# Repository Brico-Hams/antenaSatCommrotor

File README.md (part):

# PortableSatStation - estacion portable 145/435 MHz

**BricoHams · documentacion de ingenieria y montaje**

Accesos: [catalogo visual de todos los componentes inventariados](docs/assembly/components/README.md),
[instalacion visual y configuracion](docs/assembly/06-instalacion.md),
[montaje por modulos y conjunto](docs/assembly/README.md) y
[revision del proyecto y limites de verificacion](docs/PROJECT-REVIEW.md).

Laboratorio: [bancos y procedimientos reales](docs/testing/09-laboratorio.md),
[101 hojas de ensayo imprimibles](docs/testing/laboratorio/cuaderno.html) y
[registros CSV rellenables por ensayo/componente](docs/testing/laboratorio/README.md).
Incluye [NanoVNA](docs/testing/10-nanovna.md) y calibraciones; sin resultados
fisicos precargados ni autorizacion TX implicita.

## Nueva antena portable PF-01

El [rediseno PF-01](docs/ANTENNA-PORTABLE.md) toma como referencia visual
el cuerpo axial y los elementos radiales del video facilitado, sin copiar
medidas ni suponer compatibilidad RF. Propone boom dielectrico seccionado,
cuatro cassettes plegables y ocho puntas VHF desmontables. Objetivo de
paquete mecanico: **170 x 140 x 300 mm**, con verificacion geometrica
nominal, no ensayo de una antena fabricada.

Incluye [vista recogida](docs/assembly/portable/PF-folded.svg),
[BOM propia](bom/antenna-portable.csv), CAD, mallas candidatas y pruebas.
Es la nueva candidata de portabilidad; el rotor y los ejemplos anteriores
mantienen la antena historica hasta cualificar RF, masa, CG y montaje PF-01.

## Tres opciones TX/RX con previo de recepcion

La [comparativa de antenas](docs/ANTENNA-OPTIONS.md) permite escoger PF-01,
[Eggbeater](docs/ANTENNA-EGGBEATER.md) o [QFH](docs/ANTENNA-QFH.md).
Se incluyen modelos separados 145/435 MHz, vistas, BOM y montaje.
[Comunicaciones contrastadas con AMSAT](docs/SATELLITE-COMMS.md) y
[previo con bypass TX](docs/ANTENNA-PREAMPS.md): **25 W como techo de
diseno**, una sola cadena TX; sin homologacion ni habilitacion del PA.
Las redes QRP anteriores no quedan aprobadas para esa potencia.

## Idiomas / Languages / Nyelvek

La documentacion se prepara en espanol, ingles y hungaro. Las ediciones
inglesa y hungara estan en traduccion/sincronizacion y no se consideran
completas hasta comprobar cobertura y correspondencia con la revision
tecnica vigente. El indice de idiomas se enlazara al finalizar esas pruebas.
Los textos originales de licencias de terceros se conservan sin alteracion.

## Costes y materiales de referencia

La ampliacion incorporara precios de referencia en EUR para componentes,
materiales de montaje y consumibles, con cantidad, modelo/revision, fecha,
fuentes, IVA y portes. El promedio se calculara solamente con cotizaciones
comparables; una sola observacion se identificara como tal. Componentes
todavia sin modelo aprobado tendran una provision orientativa claramente
separada o precio pendiente, nunca coste cero ni precio inventado.
Las herramientas reutilizables se presupuestaran aparte del coste de la
estacion. Los pasos ilustrados se relacionaran con los identificadores de
la BOM para distinguir piezas, cables, fijaciones y materiales externos.
Las observaciones y categorias pendientes se conservan en
[reference-prices.csv](bom/reference-prices.csv), con metodo y limites en
[REFERENCE-PRICES.md](docs/REFERENCE-PRICES.md). El subconjunto electronico
cotizado suma 1313.90 EUR sin IVA normalizado; no es el coste de la estacion
completa. La recopilacion sigue abierta y no constituye presupuesto cerrado.

Diseno original modular de una estacion de radioaficionado para satelites:
antena plegable de dos bandas, rotor AZ/EL de dos ejes, controlador ESP32
con AP web y seguimiento local, compartimento RF desmontable y soporte RT3S.

**Autores actuales:** Anatol EA5KAO, Diego EA5JEF y Pedro Roca Molina.
Referencia de divulgacion cientifica para ninos y adolescentes:
[Bricohams](https://bricohams.org).
Ver [autoria](AUTHORS.md), [agradecimientos](ACKNOWLEDGEMENTS.md) y
[aviso de responsabilidad](DISCLAIMER.md). Uso educativo siempre supervisado.

**Estado: prototipo de ingenieria, no equipo RF/mecanico certificado.**
Los resultados de compilacion, pruebas y exportacion se registran en
[VALIDATION.md](docs/VALIDATION.md). Una compilacion o un STL valido NO
demuestra ROE, ganancia, resistencia al viento ni seguridad de una
estructura montada. No fabricar en serie ni transmitir sin el protocolo
de puesta en servicio.

## Base acordada

| Aspecto | Decision |
| --- | --- |
| Bandas | 145 y 435 MHz; canales concretos segun satelite y normativa |
| Motores | Dos NEMA 14; corriente/par segun ficha del motor elegido |
| Reduccion | BASE: dos etapas de correa GT2 20:100, total 25:1; planetarios como LEGACY |
| Material | ASA para piezas mecanicas; conductores y ejes metalicos |
| Seguimiento | SGP4 en ESP32; el movil no es el motor orbital |
| Red | AP sin Internet; STA con Internet o importacion manual de TLE |
| Radio | RT3S/OpenGD77 independiente; sin CAT/PTT automatico supuesto |
| Montaje | Tripode fotografico, inserto metalico y adaptadores de boom |
| Modularidad | Antena, rotor, radio y diplexor se separan |
| Masa | <=5 kg para conjunto operativo incluido tripode, radio y cables; bateria externa excluida por eleccion posterior; objetivo <=3 kg historico |
| Carga inicial | Objetivo a ensayar: antena <=0,5 kg, CG <=30 mm del eje EL |

**Cambio de prioridad aprobado:** la variante planetaria resulto demasiado
pesada en el presupuesto preliminar (3,208-4,038 kg con alimentacion).
El usuario autoriza una transmision mas ligera para priorizar <=3 kg.
La variante BASE conserva 25:1 y 80000 microsteps/vuelta, coordinados con
firmware. La geometria de montaje aun requiere verificacion fisica;
el calculo planetario original permanece
como comparativa, no como prueba de la variante ligera.

## Ampliacion en desarrollo: radio integrada multimodo

Esta seccion recoge las peticiones posteriores a la entrega inicial.
**No son prestaciones ya verificadas del hardware anterior ni de la APK
publicada localmente.** La tabla distingue alcance solicitado y estado;
las cifras medidas se registran en [VALIDATION.md](docs/VALIDATION.md).

| Funcion | Descripcion tecnica y limites | Estado de la ampliacion |
| --- | --- | --- |
| Radio de satelites VHF/UHF | 145/435 MHz nominales, frecuencias concretas segun satelite y normativa; cadenas RX/TX independientes para full-duplex | Arquitectura RF en verificacion; dos modulos seleccionados |
| Modos analogicos | FM, AM y SSB banda lateral superior (USB); USB aqui significa modo de modulacion, no conector | Solicitados; no se anuncian posibles en un modulo exclusivamente FM |
| CAT y Doppler | Control de frecuencia RX/TX y modo desde la misma APK; correccion dependiente de velocidad radial y plan de frecuencias | Integracion nueva pendiente; RT3S conserva operacion independiente sin CAT supuesto |
| Ordenador integrado | Raspberry Pi Compute Module 5 (CM5), CM5IO oficial, alimentacion y refrigeracion, para SDR, audio, SGP4 y rotor sin ESP32 | Arquitectura elegida; rendimiento conjunto, potencia y termica pendientes |
| Portadora y PCBA | CM5IO oficial adquirida mas placa auxiliar original para movimiento/sensores/protecciones | Eleccion confirmada; Gerbers/BOM/CPL de la auxiliar en desarrollo. No se fabrica una portadora CM5 unica personalizada en esta revision |
| Modulos RF | Dos LimeSDR Mini reemplazables, uno por banda para recepcion VHF/UHF simultanea; ambos capaces de TX; SMA convencional 50 ohm | Eleccion vigente; un solo TX activo inicialmente. Salida nativa de baja potencia, no 5 W: PA lineales y filtros requieren cualificacion fisica |
| Movimiento bajo Linux | Generador de movimiento dedicado en drivers, limites NC, corte fisico de potencia y watchdog independiente | Drivers y placa nueva pendientes; no generar STEP con un bucle no determinista y declarar precision |
| GNSS/GPS | Receptor y antena para sitio, altitud y UTC de SGP4; interfaz UART y PPS solo con niveles/protocolo documentados y verificados | GNSS NMEA implementado en variante ESP32; receptor/interfaz SBC y antena por seleccionar; PPS opcional y no verificado; GNSS estacionario no da rumbo |
| Brujula | Magnetometro remoto, calibracion del conjunto instalado, declinacion por sitio/fecha y referencia de norte verdadero | Compass/magnetometro nuevo no implementado ni calibrado; sensor, montaje, interfaz y PCB pendientes; conectores opcionales previos no implican brujula funcional |
| Inclinacion/nivel | IMU mide inclinacion de la base para compensacion de inclinacion de brujula; no es elevacion de antena | IMU, montaje, interfaz y calibracion nuevos pendientes; cableado/pines TBD hasta congelar PCB |
| Posicion de ejes | Tres encoders de salida independientes AZ/EL/POL y seis finales NC independientes (dos por eje); homing y limites conservadores | Tres canales de feedback y seis entradas por disenar. Tres AS5600 comparten direccion I2C 0x36: buses separados o multiplexor concreto y verificado; no asumir bus comun |
| Audio Bluetooth | Bidireccional: recepcion a Android y envio de voz/AFSK hacia radio; transporte PCM transparente separado del BLE del rotor | Protocolo y caudal en desarrollo; no atribuir audio a las tramas de control actuales |
| Audio local | Altavoz pequeno y microfono integrados; accesorio externo tipo Baofeng/K1 con jacks separados de 3,5/2,5 mm | No son conectores SMA ni de alimentacion; pinout, bias, PTT y compatibilidad exacta pendientes; no cablear por apariencia |
| SSTV en Android | Recepcion y reconstruccion de imagenes ISS PD120/PD180 desde audio | Decodificador y vectores de prueba en desarrollo |
| Funciones tipo Look4Sat/Robot36 | Primera version acordada: catalogo/pases, mapa/radar, avisos, frecuencias/Doppler, tres ejes, SSTV ISS y mensajeria APRS | Matriz funcional y desarrollo por etapas; no se promete paridad completa ni todos los modos Robot36 |
| Digitales en Android | Bell202 AFSK1200, AX.25 con NRZI, bit stuffing y CRC; interpretacion APRS | Desarrollo y pruebas PCM pendientes; no incluye automaticamente otros protocolos digitales |
| Mensajes APRS | Recepcion, redaccion y envio entre indicativos, destinatario, ID y ACK/rej | Codificacion de audio y transporte RF se verifican por separado; un WAV no demuestra transmision ni entrega |
| SMS celular | No solicitado en la seleccion final: APRS entre indicativos no es SMS a un numero de telefono | Sin pasarela movil ni promesa de entrega |
| PCB/Gerbers actualizados | Nueva portadora de ordenador, motores, audio y protecciones, con modulos RF desmontables | Revision separada pendiente de componentes/pinouts; no usar la aprobacion ERC/DRC anterior |
| Ensamblaje JLCPCB | Paquete de Gerbers/taladros, BOM PCBA y CPL pick-and-place con referencias, coordenadas, cara y rotacion; listado separado de modulos/manual/DNP | Solicitado; pendiente de placa rutada, LCSC exactos y verificacion. No se ha enviado una orden |
| Caja y energia | Branding Bricohams, acceso a conectores, blindaje RF metalico, ventilacion, bateria y protecciones | Reabrir cotas, consumo, temperatura y masa tras seleccionar hardware |
| Autonomia | Objetivo 2 horas con dos receptores activos y transmision intermitente; incluir CM5, Bluetooth, sensores y tres ejes | Consumo, porcentaje TX, capacidad util y eficiencia pendientes de medida; no duracion garantizada |
| Tercer eje POL | Motor para giro axial limitado de la antena, posicion calibrada, limites fisicos y paso protegido de coaxiales | Diseno y recalculo de masa, cargas, transmision y tres canales de motor en desarrollo |
| Seleccion RHCP/LHCP | Conmutacion RF de alimentacion/fase en antena circular compatible, distinta del giro mecanico POL | Redes por banda y conmutacion con TX inhibido pendientes de diseno y medida |
| Conectores RF | SMA convencional de 50 ohm en antena, diplexor VHF/UHF, hibrido/puertos CP, LimeSDR/radio y bulkheads | Eleccion vigente para aligerar; no RP-SMA, BNC de base ni cadenas de adaptadores. Verificar pin/socket central y genero de acoplamiento en cada pieza; masa, soporte, alivio y par del fabricante TBD. BNC solo opcion heredada |
| USB-C | Preferencia para alimentacion y datos; conservar SMA RF, K1 audio y Bluetooth bidireccional | Verificar rol host/provisionamiento, velocidad, tension y negociacion/cable de potencia por puerto; no asumir un unico puerto para todo |
| Alimentacion Powerpole y fusibles | Powerpole rojo/negro en enlace bateria externa/estacion, fusible principal cerca del positivo de bateria y fusibles por rama CM5/motores/RF | Seleccionar contactos/cable/portafusibles DC y calibres segun carga, inrush y proteccion del conductor; BMS no sustituye fusibles |
| EMI de alimentacion | Evaluar choque de modo comun, filtro diferencial amortiguado y desacoplos por rama; separar retorno/potencia de motores, conversores y RF | Corriente/saturacion/DCR, estabilidad del convertidor, transitorios y ruido recibido requieren medidas; no aislamiento RF garantizado |
| Sistema operativo BricoHams | Derivado de Raspberry Pi OS oficial ARM64 para CM5, banner/branding originales, dependencias y servicios del proyecto, aprovisionamiento privado local | Receta/CI en desarrollo; no imagen arrancada o flasheada verificada. Arranque sin movimiento/PTT y puesta en servicio explicita |

Las referencias [(tr)uSDX](https://dl2man.de/) y
[uSDX SOTA](https://antrak.org.tr/blog/usdx-sota-modular-all-mode-sdr-hf-transceiver-for-qrp-operations/)
orientan modularidad, formato y control CAT, pero son equipos **HF**:
no se escalan a 145/435 MHz cambiando solamente el firmware.
El [ATU-100](https://github.com/Dfinitski/N7DDC-ATU-100-mini-and-extended-boards)
es un acoplador, no un transceptor, filtro de aislamiento o diplexor VHF/UHF.
No se copian sus disenos ni se sustituyen sus licencias por las del proyecto.

Para full-duplex se deben medir aislamiento, bloqueo y desensibilizacion
del receptor durante TX en ambas combinaciones VHF/UHF, ademas de ROE,
armónicos y temperatura. Ningun valor de potencia, sensibilidad, autonomia,
latencia o precision de esta ampliacion se considera garantizado.
PTT debe quedar desactivado en arranque, fallo, perdida de enlace o expiracion
del permiso; transmision requiere autorizacion y puesta en servicio fisica.
La compresion de voz y la supresion de ruido pueden impedir SSTV/AFSK;
una conexion Bluetooth correcta no prueba que el audio digital sea util.
Girar una antena circular alrededor de su eje no invierte RHCP/LHCP:
la seleccion de mano necesita una red RF adecuada y ensayos de relacion
axial, fase y aislamiento. El tercer motor no existia en el rotor AZ/EL
anterior; sus drivers, limites y presupuesto no cubren el nuevo eje.

La primera entrega ESP32, su firmware/WebFlash, la APK y Gerbers anteriores
siguen siendo la variante documentada de referencia, no una implementacion
de la radio nueva. ### Matriz de variantes y evidencia (AUD-06)

| Generacion | Contenido | Pruebas que le aplican | Estado |
| --- | --- | --- | --- |
| ESP32 + RT3S (primera entrega) | ESP32 SGP4, WebFlash, APK ESP32 | 29 pruebas JVM, Node, firmware | Referencia historica; NO es aceptacion de CM5 |
| Intermedia (1-2 SDR) | Etapas del ADR-024 a ADR-026 | Pruebas de contrato de la etapa | Superada |
| CM5 + 2 LimeSDR Mini + AZ/EL/POL | Auxiliar CM5 rutada, Android CM5 | 58 pruebas JVM, 377 comprobaciones de contrato, ERC/DRC 0/0 | Prototipo DIGITAL; NO FABRICAR, NO ENERGIZAR, NO HABILITAR PTT |

Digital, fabricable y seguro operacionalmente son hitos distintos. Resultados
heredados de una generacion no se presentan como aceptacion de otra.

Si se adopta Raspberry Pi, su instalacion/aprovisionamiento
sera distinto de WebFlash ESP32. Consulte las decisiones
[ADR-024 a ADR-026](docs/ARCHITECTURE.md) y la trazabilidad
[R25 a R33](docs/REQUIREMENTS.md).

### Ubicacion, orientacion y sensores

El GNSS quieto **no mide el rumbo de la estacion**: proporciona sitio/UTC;
un rumbo deducido del movimiento no sustituye al norte verdadero del rotor.
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
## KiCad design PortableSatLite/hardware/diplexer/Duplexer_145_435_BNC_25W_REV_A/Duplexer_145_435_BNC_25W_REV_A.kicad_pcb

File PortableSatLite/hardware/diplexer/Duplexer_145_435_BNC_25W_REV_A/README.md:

DUPLEXER 145 / 435 MHz — BNC — 25 W TARGET — REV A

Architecture
  J1 ANT -> 5th-order Chebyshev LPF -> J2 VHF
  J1 ANT -> 5th-order Chebyshev HPF -> J3 UHF

Filter values are based on the published KI0AG 2m/70cm micro-duplexer:
  LPF: 68 nH, 18 pF, 100 nH, 18 pF, 68 nH
  HPF: 4.7 pF, 16 nH, 3.1 pF, 16 nH, 4.7 pF

Target bands:
  VHF: 144–146 MHz, nominal 145 MHz
  UHF: 430–440 MHz, nominal 435 MHz
  System impedance: 50 ohm
  Power target: 25 W

25 W NOTE
The published KI0AG board was described as a 10 W design. This REV A adapts the
component technology and mechanical construction for a 25 W target, but it is
NOT a laboratory-validated 25 W rating. Verify with a 50-ohm dummy load and VNA.
Start at low power and increase progressively. Check insertion loss, return loss,
and inter-port isolation before connecting radios.

BNC
J1-J3 are specified as TE Connectivity 5415025-1, 50 ohm, 4 GHz, right-angle,
panel-mount, through-hole BNC. The manufacturer explicitly says to use its product
drawing for design activity. The custom footprint in this project is a working
prototype footprint; VERIFY the exact hole pattern against the manufacturer's
drawing before ordering PCBs.

PCB
  80 x 60 mm
  2-layer FR-4, 1.6 mm
  2 oz copper recommended
  Full B.Cu ground plane
  F.Cu ground guard + stitching vias
  Metal enclosure strongly recommended

Tuning
  Measure all 3 ports with a VNA at low power.
  Tune air-core inductors and, if needed, replace C4 by 3.0/3.3 pF or add a tiny
  parallel C0G tuning pad. Do not apply 25 W until the RF response is verified.

Files
  *.kicad_pcb : PCB
  *.kicad_sch : KiCad 8 schematic project record (textual engineering schematic)
  *.sch       : legacy KiCad schematic with actual component symbols; open and
                save in KiCad to convert to a native .kicad_sch.
  fabrication/ : Gerber and Excellon files

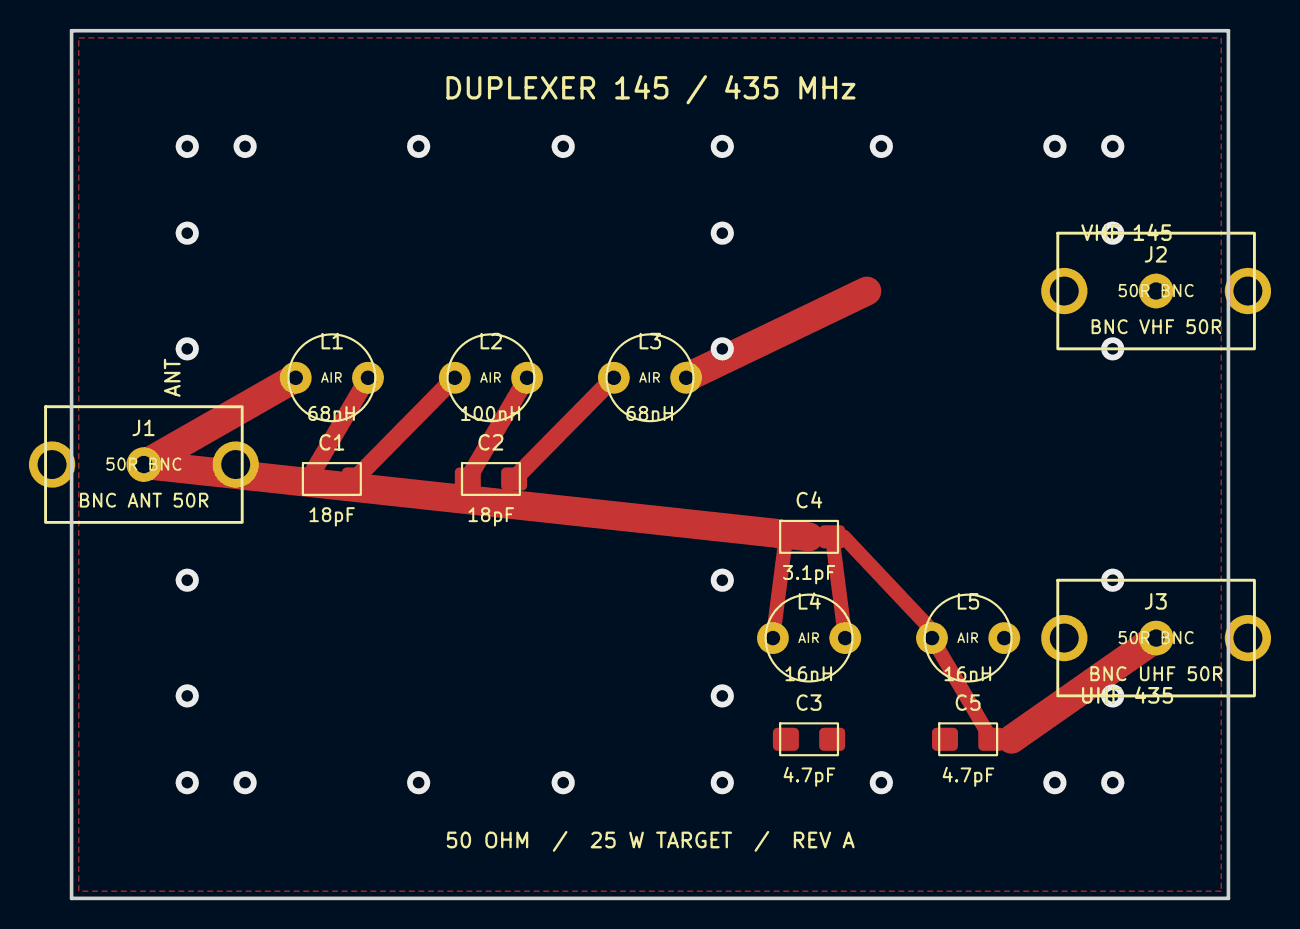
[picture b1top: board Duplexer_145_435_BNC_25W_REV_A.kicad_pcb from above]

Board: 2 copper layers, 80.0 x 60.0 mm, 13 parts (0 on the bottom side), 8 nets.

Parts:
C1: 18pF; C1
C2: 18pF; C2
C3: 4.7pF; C3
C4: 3.1pF; C4
C5: 4.7pF; C5
J1: BNC ANT 50R; J1
J2: BNC VHF 50R; J2
J3: BNC UHF 50R; J3
L1: 68nH; L1
L2: 100nH; L2
L3: 68nH; L3
L4: 16nH; L4
L5: 16nH; L5

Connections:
ANT: C3.1, J1.1, L1.1
GND: C1.2, C2.2, J1.2, J1.3, J2.2, J2.3, J3.2, J3.3, L4.2, L5.2
HP1: C3.2, C4.1, L4.1
HP2: C4.2, C5.1, L5.1
LP1: C1.1, L1.2, L2.1
LP2: C2.1, L2.2, L3.1
UHF: C5.2, J3.1
VHF: J2.1, L3.2

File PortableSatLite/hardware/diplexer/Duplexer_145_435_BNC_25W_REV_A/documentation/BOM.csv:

Ref,Value,Footprint/part,Qty,Notes
J1,BNC ANT,TE Connectivity 5415025-1,1,"50 ohm, panel mount, right angle, THT"
J2,BNC VHF,TE Connectivity 5415025-1,1,"50 ohm, panel mount, right angle, THT"
J3,BNC UHF,TE Connectivity 5415025-1,1,"50 ohm, panel mount, right angle, THT"
L1,68 nH,AIR-COIL-4MM,1,"~5 turns, 0.8-1.0 mm Cu, tune on VNA"
C1,18 pF,C0G-HV-1206,1,"1 kV preferred, C0G/NP0"
L2,100 nH,AIR-COIL-4MM,1,"~6 turns, 0.8-1.0 mm Cu, tune on VNA"
C2,18 pF,C0G-HV-1206,1,"1 kV preferred, C0G/NP0"
L3,68 nH,AIR-COIL-4MM,1,"~5 turns, 0.8-1.0 mm Cu, tune on VNA"
C3,4.7 pF,C0G-HV-1206,1,"1 kV preferred, C0G/NP0"
L4,16 nH,AIR-COIL-4MM,1,"~2.5 turns, 0.8-1.0 mm Cu, tune on VNA"
C4,3.1 pF,C0G-HV-1206,1,1 kV preferred; 3.0 pF + parasitic is acceptable
L5,16 nH,AIR-COIL-4MM,1,"~2.5 turns, 0.8-1.0 mm Cu, tune on VNA"
C5,4.7 pF,C0G-HV-1206,1,1 kV preferred
PCB,80 x 60 mm,"2-layer FR-4, 1.6 mm, 2 oz Cu",1,ENIG preferred; metal enclosure recommended
J1-J3,BNC 50 ohm,TE Connectivity 5415025-1,3,Verify mechanical drawing before fabrication

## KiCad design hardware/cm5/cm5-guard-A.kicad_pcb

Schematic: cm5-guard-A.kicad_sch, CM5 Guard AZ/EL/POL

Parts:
C1, C2, C10, C11: 1u; C_0603_1608Metric; MPN GRM188R71C105KA12D
C3, C4, C5, C6, C7, C8, C9, C12, C13, C14, C15, C17, C18, C19, C20, C21, C22, C23, C24, C25: 100n; C_0603_1608Metric; MPN GRM188R71C104KA01D
C16: 100n; C_0603_1608Metric; MPN GRM188R71C104KA01D; not fitted
C80: 47u 50V candidate; CP_Radial_D6.3mm_P2.50mm; MPN EEU-FR1H470; not fitted
D1: BZT52C12 12V; D_SOD-123; MPN BZT52C12-7-F; not fitted
D2: SMBJ18A candidate; D_SMB; MPN SMBJ18A; not fitted
F1: MAIN INSERT TBD - EMPTY; FuseHolder_Blade_ATO_Littelfuse_FLR_178.6165; MPN 178.6165.0001; not fitted
F2, F3, F4, F5, F6: BRANCH INSERT TBD - EMPTY; FuseHolder_Blade_ATO_Littelfuse_FLR_178.6165; MPN 178.6165.0001; not fitted
J1: CM5IO GPIO VIO=3V3 ONLY; IDC-Header_2x20_P2.54mm_Vertical; MPN 3020-40-0300-00
J2: ISOLATED 5V external PSU; PinHeader_1x02_P2.54mm_Vertical; not fitted
J3: AZ AS5600 0x36; JST_PH_B4B-PH-K_1x04_P2.00mm_Vertical; MPN B4B-PH-K-S(LF)(SN)
J4: EL AS5600 0x36; JST_PH_B4B-PH-K_1x04_P2.00mm_Vertical; MPN B4B-PH-K-S(LF)(SN)
J5: POL AS5600 0x36; JST_PH_B4B-PH-K_1x04_P2.00mm_Vertical; MPN B4B-PH-K-S(LF)(SN)
J6: LIS3MDL; JST_PH_B4B-PH-K_1x04_P2.00mm_Vertical; MPN B4B-PH-K-S(LF)(SN)
J7: LSM6DSOX; JST_PH_B4B-PH-K_1x04_P2.00mm_Vertical; MPN B4B-PH-K-S(LF)(SN)
J8: GNSS PID746 custom harness; PinHeader_1x05_P2.54mm_Vertical; MPN M20-9990545
J9: AZ_LIMIT_MIN_N NC contact; PinHeader_1x02_P2.54mm_Vertical; MPN M20-9990245
J10: AZ_LIMIT_MAX_N NC contact; PinHeader_1x02_P2.54mm_Vertical; MPN M20-9990245
J11: EL_LIMIT_MIN_N NC contact; PinHeader_1x02_P2.54mm_Vertical; MPN M20-9990245
J12: EL_LIMIT_MAX_N NC contact; PinHeader_1x02_P2.54mm_Vertical; MPN M20-9990245
J13: POL_LIMIT_MIN_N NC contact; PinHeader_1x02_P2.54mm_Vertical; MPN M20-9990245
J14: POL_LIMIT_MAX_N NC contact; PinHeader_1x02_P2.54mm_Vertical; MPN M20-9990245
J15: E-stop isolated AUX NC only; PinHeader_1x02_P2.54mm_Vertical; MPN M20-9990245
J16: AZ v1.5 LEFT top-view; PinSocket_1x08_P2.54mm_Vertical; MPN M20-7820842
J17: AZ v1.5 RIGHT top-view; PinSocket_1x08_P2.54mm_Vertical; MPN M20-7820842
J18: AZ MOTOR; rating TBD; PinHeader_1x04_P2.54mm_Vertical; not fitted
J19: EL v1.5 LEFT top-view; PinSocket_1x08_P2.54mm_Vertical; MPN M20-7820842
J20: EL v1.5 RIGHT top-view; PinSocket_1x08_P2.54mm_Vertical; MPN M20-7820842
J21: EL MOTOR; rating TBD; PinHeader_1x04_P2.54mm_Vertical; not fitted
J22: POL v1.5 LEFT top-view; PinSocket_1x08_P2.54mm_Vertical; MPN M20-7820842
J23: POL v1.5 RIGHT top-view; PinSocket_1x08_P2.54mm_Vertical; MPN M20-7820842
J24: POL MOTOR; rating TBD; PinHeader_1x04_P2.54mm_Vertical; not fitted
J25: AZ FAULT isolated OD only; PinHeader_1x02_P2.54mm_Vertical; MPN M20-9990245
J26: EL FAULT isolated OD only; PinHeader_1x02_P2.54mm_Vertical; MPN M20-9990245
J27: POL FAULT isolated OD only; PinHeader_1x02_P2.54mm_Vertical; MPN M20-9990245
J28: External fused DC E-stop motor supply - TBD; PinHeader_1x02_P2.54mm_Vertical; not fitted
J29: Qualified isolated PA faults only; PinHeader_1x03_P2.54mm_Vertical; MPN M20-9990345
J30: VHF PTT external limits TBD; PinHeader_1x02_P2.54mm_Vertical; MPN M20-9990245
J31: UHF PTT external limits TBD; PinHeader_1x02_P2.54mm_Vertical; MPN M20-9990245
J32: VHF actual isolated feedback; PinHeader_1x02_P2.54mm_Vertical; MPN M20-9990245
J33: UHF actual isolated feedback; PinHeader_1x02_P2.54mm_Vertical; MPN M20-9990245
J34: USB4105-GF-A USB2 DEVICE ONLY; USB_C_Receptacle_GCT_USB4105-xx-A_16P_TopMnt_Horizontal; MPN USB4105-GF-A; not fitted
J35: External USB2 device (no codec included); PinHeader_1x04_P2.54mm_Vertical; not fitted
J36: VHF_FEED_IN; SMA_Amphenol_132134_Vertical; MPN 132134
J37: VHF_FEED_OUT; SMA_Amphenol_132134_Vertical; MPN 132134
J38: UHF_FEED_IN; SMA_Amphenol_132134_Vertical; MPN 132134
J39: UHF_FEED_OUT; SMA_Amphenol_132134_Vertical; MPN 132134
J40: LOCAL NO REARM button; PinHeader_1x02_P2.54mm_Vertical; MPN M20-9990245
J41: Powerpole pigtail AFTER pack fuse and disconnect; TerminalBlock_Phoenix_MKDS-3-2-5.08_1x02_P5.08mm_Horizontal; MPN 1711725; not fitted
J42: DC-RATED EXTERNAL ESTOP OUT; TerminalBlock_Phoenix_MKDS-3-2-5.08_1x02_P5.08mm_Horizontal; MPN 1711725; not fitted
J43: EXTERNAL QUALIFIED USB-C PD CONVERTER; TerminalBlock_Phoenix_MKDS-3-2-5.08_1x02_P5.08mm_Horizontal; MPN 1711725; not fitted
J44: VHF PA external; TerminalBlock_Phoenix_MKDS-3-2-5.08_1x02_P5.08mm_Horizontal; MPN 1711725; not fitted
J45: UHF PA external; TerminalBlock_Phoenix_MKDS-3-2-5.08_1x02_P5.08mm_Horizontal; MPN 1711725; not fitted
J46: EXTERNAL ISOLATED 5V converter primary; TerminalBlock_Phoenix_MKDS-3-2-5.08_1x02_P5.08mm_Horizontal; MPN 1711725; not fitted
L1: WE-CMB 744824622 2.2mH 6A candidate; WE744824622; MPN 744824622; not fitted
NT1: MOTOR_LOGIC STAR REFERENCE; NetTie-2_SMD_Pad2.0mm
Q1, Q2, Q3, Q4, Q5, Q6: 2N7002; SOT-23; MPN 2N7002,215
Q7: AOD4185 -40V candidate; TO-252-2; MPN AOD4185; not fitted
R1, R2, R4, R5, R6, R7, R8, R9, R10, R11, R12, R13: 4.7k; R_0603_1608Metric; MPN RC0603FR-074K7L
R3, R14, R15, R16, R17, R18, R19, R20, R21, R23, R24, R25, R26, R27, R28, R29, R30, R31, R32, R33, R34, R35, R36, R37, R38, R39, R40, R41, R42, R43, R45, R46, R48, R49, R50, R51: 10k; R_0603_1608Metric; MPN RC0603FR-0710KL
R22: 1M; R_0603_1608Metric; MPN RC0603FR-071ML
R44, R47: 1k; R_0603_1608Metric; MPN RC0603FR-071KL
R52: 100k; R_0603_1608Metric; MPN RC0603FR-07100KL; not fitted
R53, R54: 5.1k; R_0603_1608Metric; MPN RC0603FR-075K1L
R80: 1R 2W DAMPING candidate; R_2512_6332Metric; MPN CRCW25121R00FKEGHP; not fitted
U1: AP2112K-3.3TRG1; SOT-23-5; MPN AP2112K-3.3TRG1
U2: MCP23017-E/SO; SOIC-28W_7.5x17.9mm_P1.27mm; MPN MCP23017-E/SO
U3: TCA9548APWR; TSSOP-24_4.4x7.8mm_P0.65mm; MPN TCA9548APWR
U4, U5, U12: SN74HC14DR; SOIC-14_3.9x8.7mm_P1.27mm; MPN SN74HC14DR
U6: SN74HC123DR; SOIC-16_3.9x9.9mm_P1.27mm; MPN SN74HC123DR
U7: SN74HC30DR; SOIC-14_3.9x8.7mm_P1.27mm; MPN SN74HC30DR
U8, U9, U14: SN74HC08DR; SOIC-14_3.9x8.7mm_P1.27mm; MPN SN74HC08DR
U10, U11: LTV-817S; SMDIP-4_W7.62mm; MPN LTV-817S
U13: SN74HC74DR; SOIC-14_3.9x8.7mm_P1.27mm; MPN SN74HC74DR

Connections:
/ALL_REQUESTS_IDLE: U13.2 (D), U14.6
/ARM_IDLE: U12.6, U14.1
/AUX_5V_ISOLATED: C1.1, J2.1, U1.1 (VIN), U1.3 (EN)
/AZ_ENABLE_REQUEST: R25.1, U2.21 (GPA0), U8.5
/AZ_EN_N: J16.1, Q1.3 (D), R30.2
/AZ_GATE: Q1.1 (G), R32.1, U8.6
/AZ_LIMIT_MAX_N: C4.1, J1.29, J10.2, R15.2, U4.3
/AZ_LIMIT_MIN_N: C3.1, J1.7, J9.2, R14.2, U4.1
/AZ_M1A: J17.5, J18.1
/AZ_M1B: J17.6, J18.2
/AZ_M2A: J17.4, J18.3
/AZ_M2B: J17.3, J18.4
/BAT_FUSED: D2.1 (A1), F1.2, Q7.2 (D)
/BAT_POS: F1.1, J41.1
/BAT_PROTECTED: C16.2, D1.1 (K), F2.1, F3.1, F4.1, F5.1, F6.1, Q7.3 (S)
/CM5IO_BRANCH_FUSED: F4.2, J43.1
/DAMP_CAP_POS: C80.1, R80.2
/EL_ENABLE_REQUEST: R26.1, U2.22 (GPA1), U8.10
/EL_EN_N: J19.1, Q2.3 (D), R34.2
/EL_GATE: Q2.1 (G), R36.1, U8.8
/EL_LIMIT_MAX_N: C6.1, J1.26, J12.2, R17.2, U4.9
/EL_LIMIT_MIN_N: C5.1, J1.31, J11.2, R16.2, U4.5
/EL_M1A: J20.5, J21.1
/EL_M1B: J20.6, J21.2
/EL_M2A: J20.4, J21.3
/EL_M2B: J20.3, J21.4
/EMI_LOGIC_POS: J46.1, L1.4 (2), R80.1
/EMI_LOGIC_RETURN: C80.2, J46.2, L1.3 (4)
/ESTOP_AUX_N: C9.1, J1.19, J15.2, R20.2, U5.1
/ESTOP_OK: U5.2, U7.11
/FAULT_AZ_N: J1.18, J25.2, R33.2
/FAULT_EL_N: J1.22, J26.2, R37.2
/FAULT_POL_N: J1.37, J27.2, R41.2
/GND_LOGIC: C1.2, C2.2, C3.2, C4.2, C5.2, C6.2, C7.2, C8.2, C9.2, C10.2, C12.2, C13.2, C14.2, C15.2, C17.2, C18.2, C19.2, C20.2, C21.2, C22.2, C23.2, C24.2, C25.2, J1.6, J1.9, J1.14, J1.20, J1.25, J1.30, J1.34, J1.39, J2.2, J3.1, J4.1, J5.1, J6.1, J7.1, J8.1, J9.1, J10.1, J11.1, J12.1, J13.1, J14.1, J15.1, J16.7, J16.8, J19.7, J19.8, J22.7, J22.8, J25.1, J26.1, J27.1, J29.1, J32.1, J33.1, NT1.2, Q1.2 (S), Q2.2 (S), Q3.2 (S), Q4.2 (S), Q5.2 (S), Q6.2 (S), R23.2, R24.2, R25.2, R26.2, R27.2, R28.2, R29.2, R32.2, R36.2, R40.2, R45.2, R48.2, R51.2, U1.2 (GND), U2.10 (V_{SS}), U2.15 (A0)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
/GND_MOTOR: D2.2 (A2), J17.2, J17.8, J20.2, J20.8, J23.2, J23.8, J28.2, J41.2, J42.2, J43.2, J44.2, J45.2, L1.2 (3), NT1.1, R52.2
/GNSS_PPS: J1.13, J8.5
/GNSS_UART_RX: J1.10, J8.3
/GNSS_UART_TX: J1.8, J8.4
/I2C1_SCL: J1.5, R2.2, U2.12 (SCK), U3.22 (SCL)
/I2C1_SDA: J1.3, R1.2, U2.13 (SDA), U3.23 (SDA)
/IDLE_AV: U14.3, U14.4
/LATCH_CLEAR_N: U13.1 (~R), U14.8
/LIMIT_OK_0: U4.2, U7.1
/LIMIT_OK_1: U4.4, U7.2
/LIMIT_OK_2: U4.6, U7.3
/LIMIT_OK_3: U4.8, U7.4
/LIMIT_OK_4: U4.10, U7.5
/LIMIT_OK_5: U4.12, U7.6
/LOGIC_BAT_FUSED: F2.2, L1.1
/LOGIC_RESET: U5.4, U5.5
/LOGIC_RESET_N: U2.18 (~RESET), U5.6, U6.3 (Clr), U14.10
/MOTOR_ARM_REQUEST: J1.32, R24.1, U8.2, U12.5
/MOTOR_BRANCH_FUSED: F3.2, J42.1
/MOTOR_PERMIT: Q6.1 (G), U8.3, U8.4, U8.9, U8.12
/MOTOR_PERMIT_FEEDBACK_N: Q6.3 (D), R50.2, U2.24 (GPA3)
/PA_UHF_FAULT_N: J29.3, R43.2, U2.28 (GPA7)
/PA_VHF_FAULT_N: J29.2, R42.2, U2.27 (GPA6)
/POL_ENABLE_REQUEST: R27.1, U2.23 (GPA2), U8.13
/POL_EN_N: J22.1, Q3.3 (D), R38.2
/POL_GATE: Q3.1 (G), R40.1, U8.11
/POL_LIMIT_MAX_N: C8.1, J1.21, J14.2, R19.2, U4.13
/POL_LIMIT_MIN_N: C7.1, J1.24, J13.2, R18.2, U4.11
/POL_M1A: J23.5, J24.1
/POL_M1B: J23.6, J24.2
/POL_M2A: J23.4, J24.3
/POL_M2B: J23.3, J24.4
/POWER_GATE: C16.1, D1.2 (A), Q7.1 (G), R52.1
/PTT_UHF_FEEDBACK_N: J33.2, R49.2, U2.26 (GPA5)
/PTT_UHF_GATE: Q5.1 (G), R48.1, U9.6
/PTT_UHF_LED_A: R47.2, U11.1
/PTT_UHF_LED_K: Q5.3 (D), U11.2
/PTT_UHF_OUT_ISO: J31.1, U11.4
/PTT_UHF_REQUEST: J1.16, R29.1, U9.5, U12.11
/PTT_UHF_RETURN_ISO: J31.2, U11.3
/PTT_VHF_FEEDBACK_N: J32.2, R46.2, U2.25 (GPA4)
/PTT_VHF_GATE: Q4.1 (G), R45.1, U9.3
/PTT_VHF_LED_A: R44.2, U10.1
/PTT_VHF_LED_K: Q4.3 (D), U10.2
/PTT_VHF_OUT_ISO: J30.1, U10.4
/PTT_VHF_REQUEST: J1.15, R28.1, U9.2, U12.9
/PTT_VHF_RETURN_ISO: J30.2, U10.3
/REARMED: U13.5 (Q), U14.13
/REARM_BUTTON: C12.1, J40.2, R51.1, U12.1
/REARM_BUTTON_N: U12.2, U12.3
/REARM_CLK: U12.4, U13.3 (C)
/REARM_PERMIT: U8.1, U9.1, U9.4, U14.11
/RESET_RC: C10.1, R21.2, U5.3
/RF_UHF_GND: J38.2 (Ext), J39.2 (Ext)
/RF_UHF_LINE: J38.1 (In), J39.1 (In)
/RF_VHF_GND: J36.2 (Ext), J37.2 (Ext)
/RF_VHF_LINE: J36.1 (In), J37.1 (In)
/SAFE_N: U5.9, U7.8
/SAFE_OK: U5.8, U14.9, U14.12
/SCL_CH0: J3.4, R5.2, U3.5 (SC0)
/SCL_CH1: J4.4, R7.2, U3.7 (SC1)
/SCL_CH2: J5.4, R9.2, U3.9 (SC2)
/SCL_CH3: J6.4, R11.2, U3.11 (SC3)
/SCL_CH4: J7.4, R13.2, U3.14 (SC4)
/SDA_CH0: J3.3, R4.2, U3.4 (SD0)
/SDA_CH1: J4.3, R6.2, U3.6 (SD1)
/SDA_CH2: J5.3, R8.2, U3.8 (SD2)
/SDA_CH3: J6.3, R10.2, U3.10 (SD3)
/SDA_CH4: J7.3, R12.2, U3.13 (SD4)
/SPI1_CS0_AZ: J1.12, J16.4, R31.2
/SPI1_CS1_EL: J1.11, J19.4, R35.2
/SPI1_CS2_POL: J1.36, J22.4, R39.2
/SPI1_MISO: J1.35, J16.5, J19.5, J22.5
/SPI1_MOSI: J1.38, J16.2, J19.2, J22.2
/SPI1_SCLK: J1.40, J16.3, J19.3, J22.3
/TCA9548A_RESET_N: J1.33, R3.2, U3.3 (~RESET)
/UHF_BRANCH_FUSED: F6.2, J45.1
/UHF_IDLE: U12.10, U14.5
/USB_CC1: J34.A5 (CC1), R53.1
/USB_CC2: J34.B5 (CC2), R54.1
/USB_DM: J34.A7 (D-), J34.B7 (D-), J35.3
/USB_DP: J34.A6 (D+), J34.B6 (D+), J35.4
/USB_RETURN: J34.A1 (GND), J34.A12 (GND), J34.B1 (GND), J34.B12 (GND), J35.2, R53.2, R54.2
/USB_VBUS_DEVICE: J34.A4 (VBUS), J34.A9 (VBUS), J34.B4 (VBUS), J34.B9 (VBUS), J35.1
/V3V3: C2.1, C13.1, C14.1, C15.1, C17.1, C18.1, C19.1, C20.1, C21.1, C22.1, C23.1, C24.1, C25.1, J3.2, J4.2, J5.2, J6.2, J7.2, J8.2, J17.7, J20.7, J23.7, J40.1, R1.1, R2.1, R3.1, R4.1, R5.1, R6.1, R7.1, R8.1, R9.1, R10.1, R11.1, R12.1, R13.1, R14.1, R15.1, R16.1, R17.1, R18.1, R19.1, R20.1, R21.1, R22.1, R30.1, R31.1, R33.1, R34.1, R35.1, R37.1, R38.1, R39.1, R41.1, R42.1, R43.1, R44.1, R46.1, R47.1, R49.1, R50.1, U1.5 (VOUT), U2.9 (V_{DD}), U3.24 (VCC), U4.14 (VCC), U5.14 (VCC), U6.16 (VCC), U7.14 (VCC), U8.14 (VCC), U9.14 (VCC), U12.14 (VCC), U13.4 (~S), U13.10 (~S), U13.14 (VCC), U14.14 (VCC)
/VHF_BRANCH_FUSED: F5.2, J44.1
/VHF_IDLE: U12.8, U14.2
/VMOT_ESTOP: J17.1, J20.1, J23.1, J28.1
/WATCHDOG_HEARTBEAT: J1.23, R23.1, U6.2 (B)
/WATCHDOG_OK: U6.13 (Q), U7.12
/WD_C: C11.2, U6.14 (Cext)
/WD_RC: C11.1, R22.2, U6.15 (RCext)

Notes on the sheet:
CM5 GUARD A - ENGINEERING REVIEW ONLY - DO NOT FABRICATE / NO MOTOR OR TX OPERATION
Every net is labelled. NC contacts to GND: open wire inhibits hardware; external DC E-stop is mandatory.
Powerpole / EMI / isolated power / CM5IO PD / RF bulkhead SMA stay EXTERNAL, unresolved ratings.
POWER CANDIDATES DNP: empty fuseholders, unqualified ratings; no motor/PA/battery operation authorized.
Manual rearm latch requires healthy NC/E-stop/watchdog and arm/PTT requests LOW at local button edge.
SMA pairs are passive feed-through ONLY. No PA/filter/RHCP-LHCP integration or RF validation claimed.

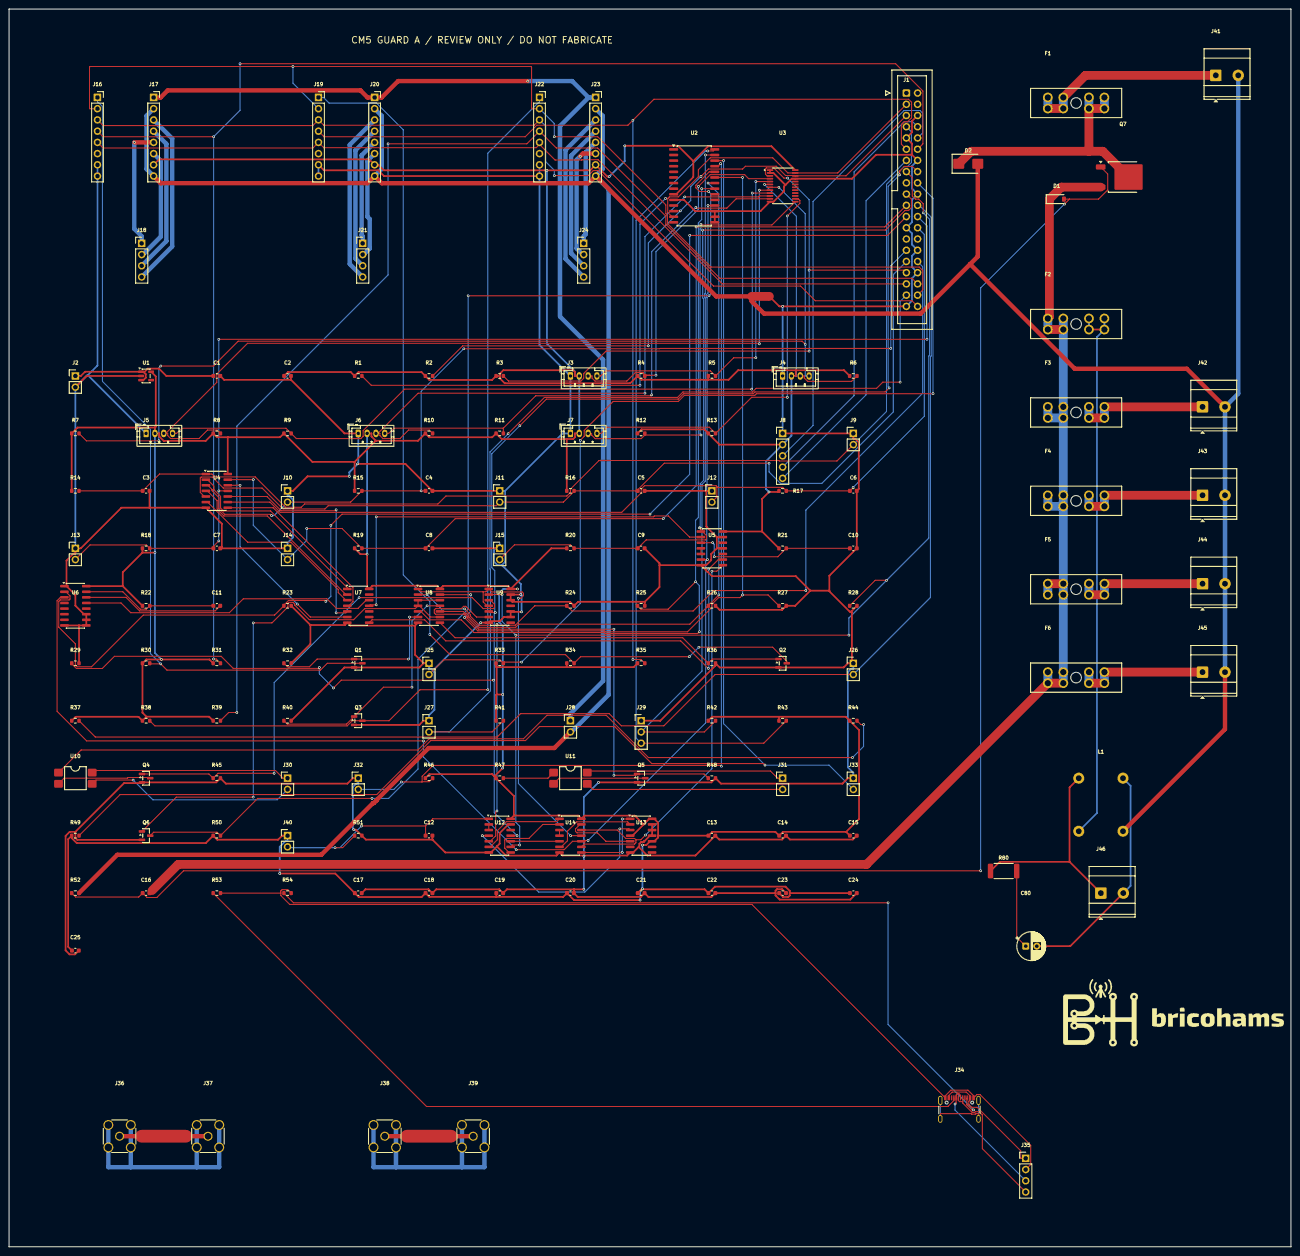
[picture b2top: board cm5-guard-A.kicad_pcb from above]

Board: 2 copper layers, 290.0 x 280.0 mm, 158 parts (0 on the bottom side), 126 nets.

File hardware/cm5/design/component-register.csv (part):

Reference,Value,Candidate MPN,KiCad footprint,DNP,Scope,Sourcing/physical verification
J1,CM5IO GPIO VIO=3V3 ONLY,3020-40-0300-00,Connector_IDC:IDC-Header_2x20_P2.54mm_Vertical,False,BOARD,NOT VERIFIED / NO LCSC CODE
J2,ISOLATED 5V external PSU,,Connector_PinHeader_2.54mm:PinHeader_1x02_P2.54mm_Vertical,True,BOARD,NOT VERIFIED / NO LCSC CODE
U1,AP2112K-3.3TRG1,AP2112K-3.3TRG1,Package_TO_SOT_SMD:SOT-23-5,False,BOARD,NOT VERIFIED / NO LCSC CODE
C1,1u,GRM188R71C105KA12D,Capacitor_SMD:C_0603_1608Metric,False,BOARD,NOT VERIFIED / NO LCSC CODE
C2,1u,GRM188R71C105KA12D,Capacitor_SMD:C_0603_1608Metric,False,BOARD,NOT VERIFIED / NO LCSC CODE
U2,MCP23017-E/SO,MCP23017-E/SO,Package_SO:SOIC-28W_7.5x17.9mm_P1.27mm,False,BOARD,NOT VERIFIED / NO LCSC CODE
R1,4.7k,RC0603FR-074K7L,Resistor_SMD:R_0603_1608Metric,False,BOARD,NOT VERIFIED / NO LCSC CODE
R2,4.7k,RC0603FR-074K7L,Resistor_SMD:R_0603_1608Metric,False,BOARD,NOT VERIFIED / NO LCSC CODE
U3,TCA9548APWR,TCA9548APWR,Package_SO:TSSOP-24_4.4x7.8mm_P0.65mm,False,BOARD,NOT VERIFIED / NO LCSC CODE
R3,10k,RC0603FR-0710KL,Resistor_SMD:R_0603_1608Metric,False,BOARD,NOT VERIFIED / NO LCSC CODE
J3,AZ AS5600 0x36,B4B-PH-K-S(LF)(SN),Connector_JST:JST_PH_B4B-PH-K_1x04_P2.00mm_Vertical,False,BOARD,NOT VERIFIED / NO LCSC CODE
R4,4.7k,RC0603FR-074K7L,Resistor_SMD:R_0603_1608Metric,False,BOARD,NOT VERIFIED / NO LCSC CODE
R5,4.7k,RC0603FR-074K7L,Resistor_SMD:R_0603_1608Metric,False,BOARD,NOT VERIFIED / NO LCSC CODE
J4,EL AS5600 0x36,B4B-PH-K-S(LF)(SN),Connector_JST:JST_PH_B4B-PH-K_1x04_P2.00mm_Vertical,False,BOARD,NOT VERIFIED / NO LCSC CODE
R6,4.7k,RC0603FR-074K7L,Resistor_SMD:R_0603_1608Metric,False,BOARD,NOT VERIFIED / NO LCSC CODE
R7,4.7k,RC0603FR-074K7L,Resistor_SMD:R_0603_1608Metric,False,BOARD,NOT VERIFIED / NO LCSC CODE
J5,POL AS5600 0x36,B4B-PH-K-S(LF)(SN),Connector_JST:JST_PH_B4B-PH-K_1x04_P2.00mm_Vertical,False,BOARD,NOT VERIFIED / NO LCSC CODE
R8,4.7k,RC0603FR-074K7L,Resistor_SMD:R_0603_1608Metric,False,BOARD,NOT VERIFIED / NO LCSC CODE
R9,4.7k,RC0603FR-074K7L,Resistor_SMD:R_0603_1608Metric,False,BOARD,NOT VERIFIED / NO LCSC CODE
J6,LIS3MDL,B4B-PH-K-S(LF)(SN),Connector_JST:JST_PH_B4B-PH-K_1x04_P2.00mm_Vertical,False,BOARD,NOT VERIFIED / NO LCSC CODE
R10,4.7k,RC0603FR-074K7L,Resistor_SMD:R_0603_1608Metric,False,BOARD,NOT VERIFIED / NO LCSC CODE
R11,4.7k,RC0603FR-074K7L,Resistor_SMD:R_0603_1608Metric,False,BOARD,NOT VERIFIED / NO LCSC CODE
J7,LSM6DSOX,B4B-PH-K-S(LF)(SN),Connector_JST:JST_PH_B4B-PH-K_1x04_P2.00mm_Vertical,False,BOARD,NOT VERIFIED / NO LCSC CODE
R12,4.7k,RC0603FR-074K7L,Resistor_SMD:R_0603_1608Metric,False,BOARD,NOT VERIFIED / NO LCSC CODE
R13,4.7k,RC0603FR-074K7L,Resistor_SMD:R_0603_1608Metric,False,BOARD,NOT VERIFIED / NO LCSC CODE
J8,GNSS PID746 custom harness,M20-9990545,Connector_PinHeader_2.54mm:PinHeader_1x05_P2.54mm_Vertical,False,BOARD,NOT VERIFIED / NO LCSC CODE
J9,AZ_LIMIT_MIN_N NC contact,M20-9990245,Connector_PinHeader_2.54mm:PinHeader_1x02_P2.54mm_Vertical,False,BOARD,NOT VERIFIED / NO LCSC CODE
R14,10k,RC0603FR-0710KL,Resistor_SMD:R_0603_1608Metric,False,BOARD,NOT VERIFIED / NO LCSC CODE
C3,100n,GRM188R71C104KA01D,Capacitor_SMD:C_0603_1608Metric,False,BOARD,NOT VERIFIED / NO LCSC CODE
U4,SN74HC14DR,SN74HC14DR,Package_SO:SOIC-14_3.9x8.7mm_P1.27mm,False,BOARD,NOT VERIFIED / NO LCSC CODE
J10,AZ_LIMIT_MAX_N NC contact,M20-9990245,Connector_PinHeader_2.54mm:PinHeader_1x02_P2.54mm_Vertical,False,BOARD,NOT VERIFIED / NO LCSC CODE
R15,10k,RC0603FR-0710KL,Resistor_SMD:R_0603_1608Metric,False,BOARD,NOT VERIFIED / NO LCSC CODE
C4,100n,GRM188R71C104KA01D,Capacitor_SMD:C_0603_1608Metric,False,BOARD,NOT VERIFIED / NO LCSC CODE
J11,EL_LIMIT_MIN_N NC contact,M20-9990245,Connector_PinHeader_2.54mm:PinHeader_1x02_P2.54mm_Vertical,False,BOARD,NOT VERIFIED / NO LCSC CODE
R16,10k,RC0603FR-0710KL,Resistor_SMD:R_0603_1608Metric,False,BOARD,NOT VERIFIED / NO LCSC CODE
C5,100n,GRM188R71C104KA01D,Capacitor_SMD:C_0603_1608Metric,False,BOARD,NOT VERIFIED / NO LCSC CODE
J12,EL_LIMIT_MAX_N NC contact,M20-9990245,Connector_PinHeader_2.54mm:PinHeader_1x02_P2.54mm_Vertical,False,BOARD,NOT VERIFIED / NO LCSC CODE
R17,10k,RC0603FR-0710KL,Resistor_SMD:R_0603_1608Metric,False,BOARD,NOT VERIFIED / NO LCSC CODE
C6,100n,GRM188R71C104KA01D,Capacitor_SMD:C_0603_1608Metric,False,BOARD,NOT VERIFIED / NO LCSC CODE
J13,POL_LIMIT_MIN_N NC contact,M20-9990245,Connector_PinHeader_2.54mm:PinHeader_1x02_P2.54mm_Vertical,False,BOARD,NOT VERIFIED / NO LCSC CODE
R18,10k,RC0603FR-0710KL,Resistor_SMD:R_0603_1608Metric,False,BOARD,NOT VERIFIED / NO LCSC CODE
C7,100n,GRM188R71C104KA01D,Capacitor_SMD:C_0603_1608Metric,False,BOARD,NOT VERIFIED / NO LCSC CODE
J14,POL_LIMIT_MAX_N NC contact,M20-9990245,Connector_PinHeader_2.54mm:PinHeader_1x02_P2.54mm_Vertical,False,BOARD,NOT VERIFIED / NO LCSC CODE
R19,10k,RC0603FR-0710KL,Resistor_SMD:R_0603_1608Metric,False,BOARD,NOT VERIFIED / NO LCSC CODE
C8,100n,GRM188R71C104KA01D,Capacitor_SMD:C_0603_1608Metric,False,BOARD,NOT VERIFIED / NO LCSC CODE
J15,E-stop isolated AUX NC only,M20-9990245,Connector_PinHeader_2.54mm:PinHeader_1x02_P2.54mm_Vertical,False,BOARD,NOT VERIFIED / NO LCSC CODE
R20,10k,RC0603FR-0710KL,Resistor_SMD:R_0603_1608Metric,False,BOARD,NOT VERIFIED / NO LCSC CODE
C9,100n,GRM188R71C104KA01D,Capacitor_SMD:C_0603_1608Metric,False,BOARD,NOT VERIFIED / NO LCSC CODE
U5,SN74HC14DR,SN74HC14DR,Package_SO:SOIC-14_3.9x8.7mm_P1.27mm,False,BOARD,NOT VERIFIED / NO LCSC CODE
R21,10k,RC0603FR-0710KL,Resistor_SMD:R_0603_1608Metric,False,BOARD,NOT VERIFIED / NO LCSC CODE
C10,1u,GRM188R71C105KA12D,Capacitor_SMD:C_0603_1608Metric,False,BOARD,NOT VERIFIED / NO LCSC CODE
U6,SN74HC123DR,SN74HC123DR,Package_SO:SOIC-16_3.9x9.9mm_P1.27mm,False,BOARD,NOT VERIFIED / NO LCSC CODE
R22,1M,RC0603FR-071ML,Resistor_SMD:R_0603_1608Metric,False,BOARD,NOT VERIFIED / NO LCSC CODE
C11,1u,GRM188R71C105KA12D,Capacitor_SMD:C_0603_1608Metric,False,BOARD,NOT VERIFIED / NO LCSC CODE
R23,10k,RC0603FR-0710KL,Resistor_SMD:R_0603_1608Metric,False,BOARD,NOT VERIFIED / NO LCSC CODE
U7,SN74HC30DR,SN74HC30DR,Package_SO:SOIC-14_3.9x8.7mm_P1.27mm,False,BOARD,NOT VERIFIED / NO LCSC CODE
U8,SN74HC08DR,SN74HC08DR,Package_SO:SOIC-14_3.9x8.7mm_P1.27mm,False,BOARD,NOT VERIFIED / NO LCSC CODE
U9,SN74HC08DR,SN74HC08DR,Package_SO:SOIC-14_3.9x8.7mm_P1.27mm,False,BOARD,NOT VERIFIED / NO LCSC CODE
R24,10k,RC0603FR-0710KL,Resistor_SMD:R_0603_1608Metric,False,BOARD,NOT VERIFIED / NO LCSC CODE
R25,10k,RC0603FR-0710KL,Resistor_SMD:R_0603_1608Metric,False,BOARD,NOT VERIFIED / NO LCSC CODE
R26,10k,RC0603FR-0710KL,Resistor_SMD:R_0603_1608Metric,False,BOARD,NOT VERIFIED / NO LCSC CODE
R27,10k,RC0603FR-0710KL,Resistor_SMD:R_0603_1608Metric,False,BOARD,NOT VERIFIED / NO LCSC CODE
R28,10k,RC0603FR-0710KL,Resistor_SMD:R_0603_1608Metric,False,BOARD,NOT VERIFIED / NO LCSC CODE
R29,10k,RC0603FR-0710KL,Resistor_SMD:R_0603_1608Metric,False,BOARD,NOT VERIFIED / NO LCSC CODE
J16,AZ v1.5 LEFT top-view,M20-7820842,Connector_PinSocket_2.54mm:PinSocket_1x08_P2.54mm_Vertical,False,BOARD,NOT VERIFIED / NO LCSC CODE
J17,AZ v1.5 RIGHT top-view,M20-7820842,Connector_PinSocket_2.54mm:PinSocket_1x08_P2.54mm_Vertical,False,BOARD,NOT VERIFIED / NO LCSC CODE
J18,AZ MOTOR; rating TBD,,Connector_PinHeader_2.54mm:PinHeader_1x04_P2.54mm_Vertical,True,BOARD,NOT VERIFIED / NO LCSC CODE
R30,10k,RC0603FR-0710KL,Resistor_SMD:R_0603_1608Metric,False,BOARD,NOT VERIFIED / NO LCSC CODE
R31,10k,RC0603FR-0710KL,Resistor_SMD:R_0603_1608Metric,False,BOARD,NOT VERIFIED / NO LCSC CODE
R32,10k,RC0603FR-0710KL,Resistor_SMD:R_0603_1608Metric,False,BOARD,NOT VERIFIED / NO LCSC CODE
Q1,2N7002,"2N7002,215",Package_TO_SOT_SMD:SOT-23,False,BOARD,NOT VERIFIED / NO LCSC CODE
J25,AZ FAULT isolated OD only,M20-9990245,Connector_PinHeader_2.54mm:PinHeader_1x02_P2.54mm_Vertical,False,BOARD,NOT VERIFIED / NO LCSC CODE
R33,10k,RC0603FR-0710KL,Resistor_SMD:R_0603_1608Metric,False,BOARD,NOT VERIFIED / NO LCSC CODE
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

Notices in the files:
README.md:
CERN-OHL-S-2.0; ver alcance y derechos de terceros en [NOTICE.md](NOTICE.md).
